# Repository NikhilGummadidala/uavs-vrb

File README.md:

# uavs-vrb
a board that regulates voltage

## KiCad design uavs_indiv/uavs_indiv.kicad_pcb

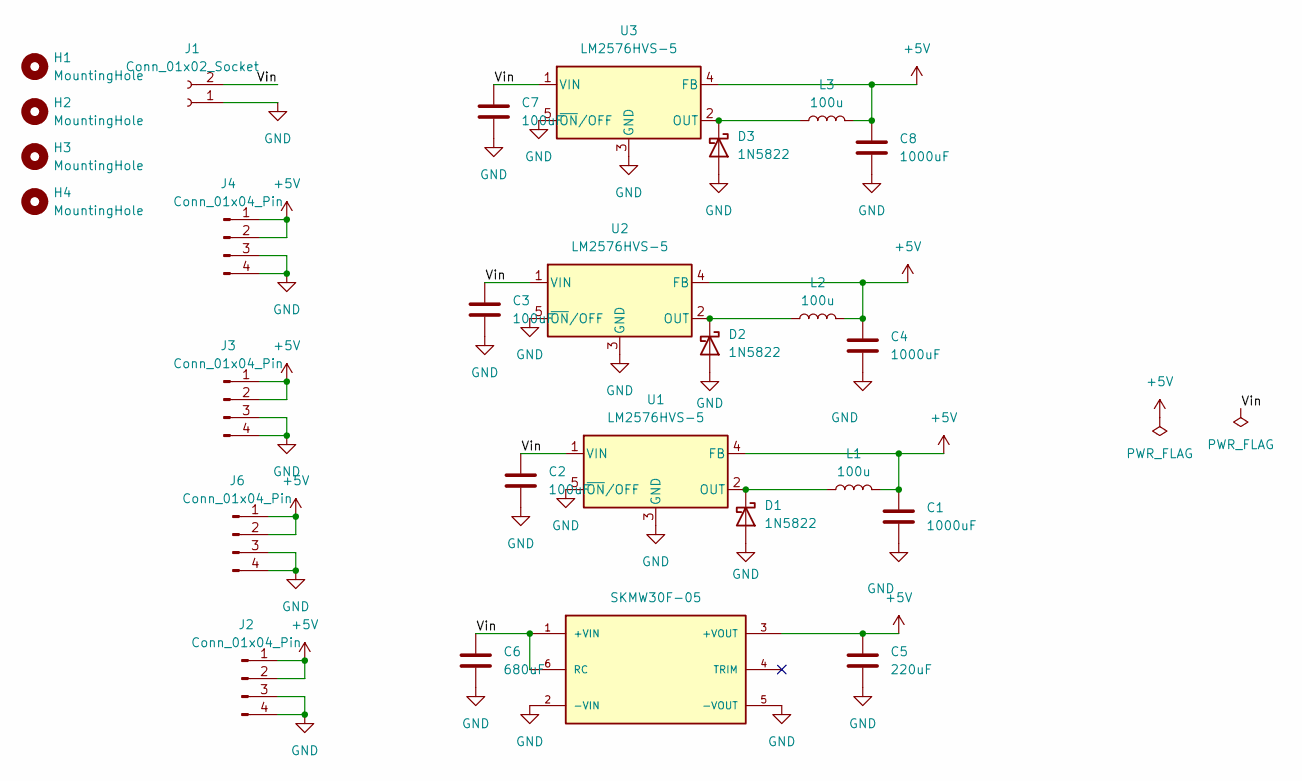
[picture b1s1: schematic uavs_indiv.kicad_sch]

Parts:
C1, C4, C8: 1000uF; capacitor1000uf
C2, C3, C7: 100uF; capacitor100uf
C5: 220uF; capacitor220uf
C6: 680uF; capacitor680uf
D1, D2, D3: 1N5822; D_DO-201AD_P15.24mm_Horizontal
H1, H2, H3, H4: MountingHole; MountingHole_2.1mm
J1: Conn_01x02_Socket; AMASS_XT60PW-F_1x02_P7.20mm_Horizontal
J2, J3, J4, J6: Conn_01x04_Pin; Molex_Micro-Fit_3.0_43650-0400_1x04_P3.00mm_Horizontal
L1, L2, L3: 100u; inductor3.5a100u
PS1: SKMW30F-05; CONV_SKMW30F-05; PARTREV 2022-05-24; DigiKey_Part_Number 1866-4667-ND
U1, U2, U3: LM2576HVS-5; TO-263-5_TabPin3

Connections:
+5V: C1.1, C4.1, C5.1, C8.1, J2.1, J2.2, J3.1, J3.2, J4.1, J4.2, J6.1, J6.2, L1.2, L2.2, L3.2, PS1.3 (+VOUT), U1.4 (FB), U2.4 (FB), U3.4 (FB)
/Vin: C2.1, C3.1, C6.1, C7.1, J1.2, PS1.1 (+VIN), PS1.6 (RC), U1.1 (VIN), U2.1 (VIN), U3.1 (VIN)
GND: C1.2, C2.2, C3.2, C4.2, C5.2, C6.2, C7.2, C8.2, D1.2 (A), D2.2 (A), D3.2 (A), J1.1, J2.3, J2.4, J3.3, J3.4, J4.3, J4.4, J6.3, J6.4, PS1.2 (-VIN), PS1.5 (-VOUT), U1.3 (GND), U1.5 (~ON/OFF), U2.3 (GND), U2.5 (~ON/OFF), U3.3 (GND), U3.5 (~ON/OFF)
unnamed: D1.1 (K), L1.1, U1.2 (OUT)
unnamed: D2.1 (K), L2.1, U2.2 (OUT)
unnamed: D3.1 (K), L3.1, U3.2 (OUT)

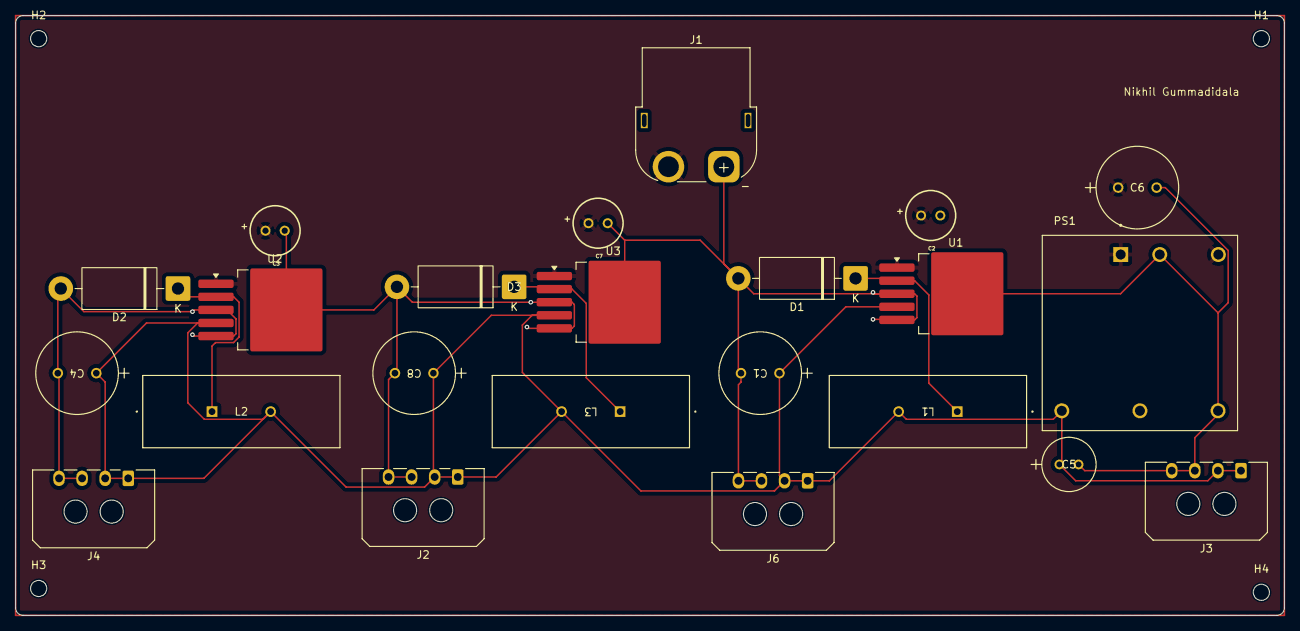
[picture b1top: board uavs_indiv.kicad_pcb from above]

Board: 2 copper layers, 165.0 x 78.0 mm, 27 parts (0 on the bottom side), 6 nets.

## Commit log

2026-02-07 version 1
    added the converters and jawn
2026-02-08 added traces
    join effort(95 - 5 split nikhil brian respectively)
2026-02-08 wtf did i just see
2026-02-28 added copper pours
2026-03-02 got rid of copper pours, added via, got rid of ground routing, fixed silkscreen
    wip:
    adding edge cuts board
    changing the thickness of the traces for power pours
2026-03-23 redidt footprints and routing
2026-04-09 changed vin traces and added name
2026-05-03 made traces bigger added space between components added screw holes added one more 5v output (unisolated)
2026-05-17 added filled copper zone for vin
